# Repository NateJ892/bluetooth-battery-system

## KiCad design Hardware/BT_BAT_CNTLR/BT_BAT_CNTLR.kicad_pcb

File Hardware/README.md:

Bluetooth Battey Bank Project

TODO:
- Upsize regulator
- Add USB protection IC
- Increase Connector Current to 1.5A each for "Fast Charging"

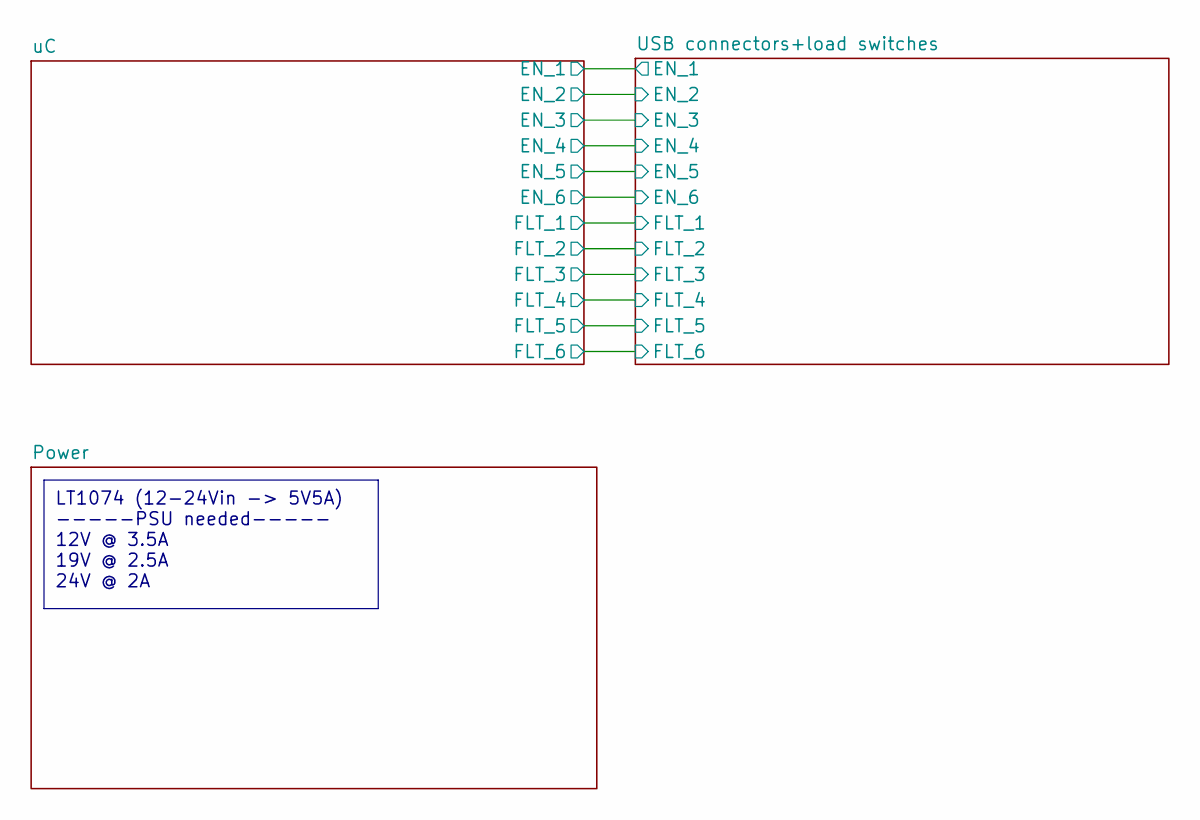
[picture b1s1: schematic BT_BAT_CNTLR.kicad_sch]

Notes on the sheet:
LT1074 (12-24Vin -> 5V5A) -----PSU needed----- 12V @ 3.5A 19V @ 2.5A 24V @ 2A

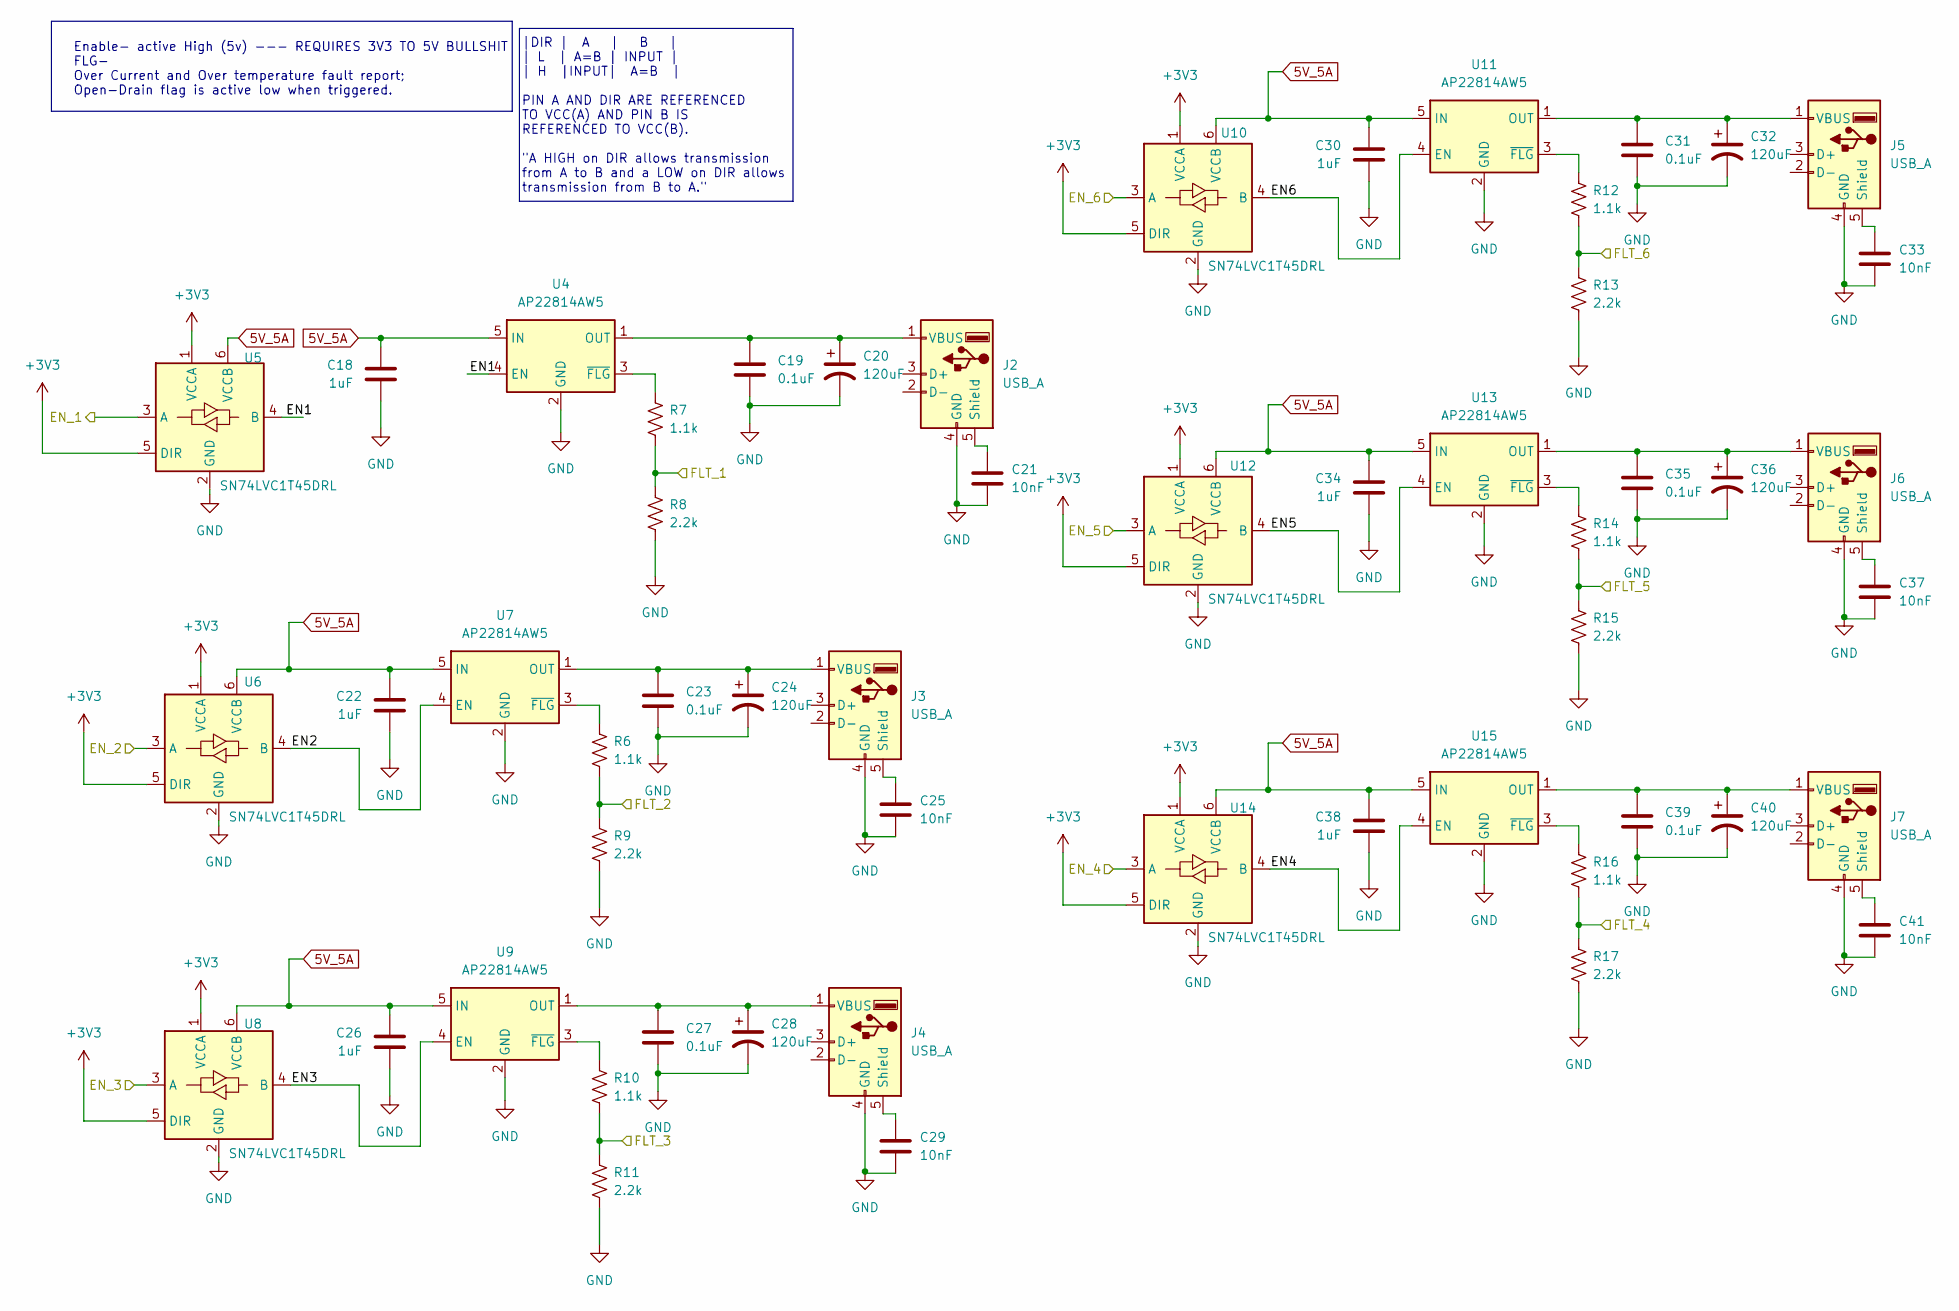
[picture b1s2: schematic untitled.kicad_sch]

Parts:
C18, C22, C26, C30, C34, C38: 1uF; C_0603_1608Metric
C19, C23, C27, C31, C35, C39: 0.1uF; C_0603_1608Metric
C20, C24, C28, C32, C36, C40: 120uF; CP_Elec_5x5.9
C21, C25, C29, C33, C37, C41: 10nF; C_0603_1608Metric
J2, J3, J4, J5, J6, J7: USB_A; USB_A_Molex_67643_Horizontal
R6, R7, R10, R12, R14, R16: 1.1k; R_0603_1608Metric
R8, R9, R11, R13, R15, R17: 2.2k; R_0603_1608Metric
U4, U7, U9, U11, U13, U15: AP22814AW5; SOT-23-5
U5, U6, U8, U10, U12, U14: SN74LVC1T45DRL; SOT-563

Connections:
5V_5A: C18.1, C22.1, C26.1, C30.1, C34.1, C38.1, U4.5 (IN), U5.6 (VCCB), U6.6 (VCCB), U7.5 (IN), U8.6 (VCCB), U9.5 (IN), U10.6 (VCCB), U11.5 (IN), U12.6 (VCCB), U13.5 (IN), U14.6 (VCCB), U15.5 (IN); also elsewhere on the board
+3V3: U5.1 (VCCA), U5.5 (DIR), U6.1 (VCCA), U6.5 (DIR), U8.1 (VCCA), U8.5 (DIR), U10.1 (VCCA), U10.5 (DIR), U12.1 (VCCA), U12.5 (DIR), U14.1 (VCCA), U14.5 (DIR); also elsewhere on the board
/USB connectors+load switches/EN1: U4.4 (EN), U5.4 (B)
/USB connectors+load switches/EN2: U6.4 (B), U7.4 (EN)
/USB connectors+load switches/EN3: U8.4 (B), U9.4 (EN)
/USB connectors+load switches/EN4: U14.4 (B), U15.4 (EN)
/USB connectors+load switches/EN5: U12.4 (B), U13.4 (EN)
/USB connectors+load switches/EN6: U10.4 (B), U11.4 (EN)
/USB connectors+load switches/EN_1: U5.3 (A); also elsewhere on the board
/USB connectors+load switches/EN_2: U6.3 (A); also elsewhere on the board
/USB connectors+load switches/EN_3: U8.3 (A); also elsewhere on the board
/USB connectors+load switches/EN_4: U14.3 (A); also elsewhere on the board
/USB connectors+load switches/EN_5: U12.3 (A); also elsewhere on the board
/USB connectors+load switches/EN_6: U10.3 (A); also elsewhere on the board
/USB connectors+load switches/FLT_1: R7.2, R8.1; also elsewhere on the board
/USB connectors+load switches/FLT_2: R6.2, R9.1; also elsewhere on the board
/USB connectors+load switches/FLT_3: R10.2, R11.1; also elsewhere on the board
/USB connectors+load switches/FLT_4: R16.2, R17.1; also elsewhere on the board
/USB connectors+load switches/FLT_5: R14.2, R15.1; also elsewhere on the board
/USB connectors+load switches/FLT_6: R12.2, R13.1; also elsewhere on the board
GND: C18.2, C19.2, C20.2, C21.2, C22.2, C23.2, C24.2, C25.2, C26.2, C27.2, C28.2, C29.2, C30.2, C31.2, C32.2, C33.2, C34.2, C35.2, C36.2, C37.2, C38.2, C39.2, C40.2, C41.2, J2.4 (GND), J3.4 (GND), J4.4 (GND), J5.4 (GND), J6.4 (GND), J7.4 (GND), R8.2, R9.2, R11.2, R13.2, R15.2, R17.2, U4.2 (GND), U5.2 (GND), U6.2 (GND), U7.2 (GND), U8.2 (GND), U9.2 (GND), U10.2 (GND), U11.2 (GND), U12.2 (GND), U13.2 (GND), U14.2 (GND), U15.2 (GND); also elsewhere on the board
unnamed: C21.1, J2.5 (Shield)
unnamed: C19.1, C20.1, J2.1 (VBUS), U4.1 (OUT)
unnamed: C25.1, J3.5 (Shield)
unnamed: C23.1, C24.1, J3.1 (VBUS), U7.1 (OUT)
unnamed: C29.1, J4.5 (Shield)
unnamed: C27.1, C28.1, J4.1 (VBUS), U9.1 (OUT)
unnamed: C33.1, J5.5 (Shield)
unnamed: C31.1, C32.1, J5.1 (VBUS), U11.1 (OUT)
unnamed: C37.1, J6.5 (Shield)
unnamed: C35.1, C36.1, J6.1 (VBUS), U13.1 (OUT)
unnamed: C41.1, J7.5 (Shield)
unnamed: C39.1, C40.1, J7.1 (VBUS), U15.1 (OUT)
unnamed: R7.1, U4.3 (~FLG)
unnamed: R6.1, U7.3 (~FLG)
unnamed: R10.1, U9.3 (~FLG)
unnamed: R12.1, U11.3 (~FLG)
unnamed: R14.1, U13.3 (~FLG)
unnamed: R16.1, U15.3 (~FLG)

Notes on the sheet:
|DIR | A | B | | L | A=B | INPUT | | H |INPUT| A=B | PIN A AND DIR ARE REFERENCED TO VCC(A) AND PIN B IS REFERENCED TO VCC(B). "A HIGH on DIR allows transmission from A to B and a LOW on DIR allows transmission from B to A."
Enable- active High (5v) --- REQUIRES 3V3 TO 5V BULLSHIT FLG- Over Current and Over temperature fault report; Open-Drain flag is active low when triggered.

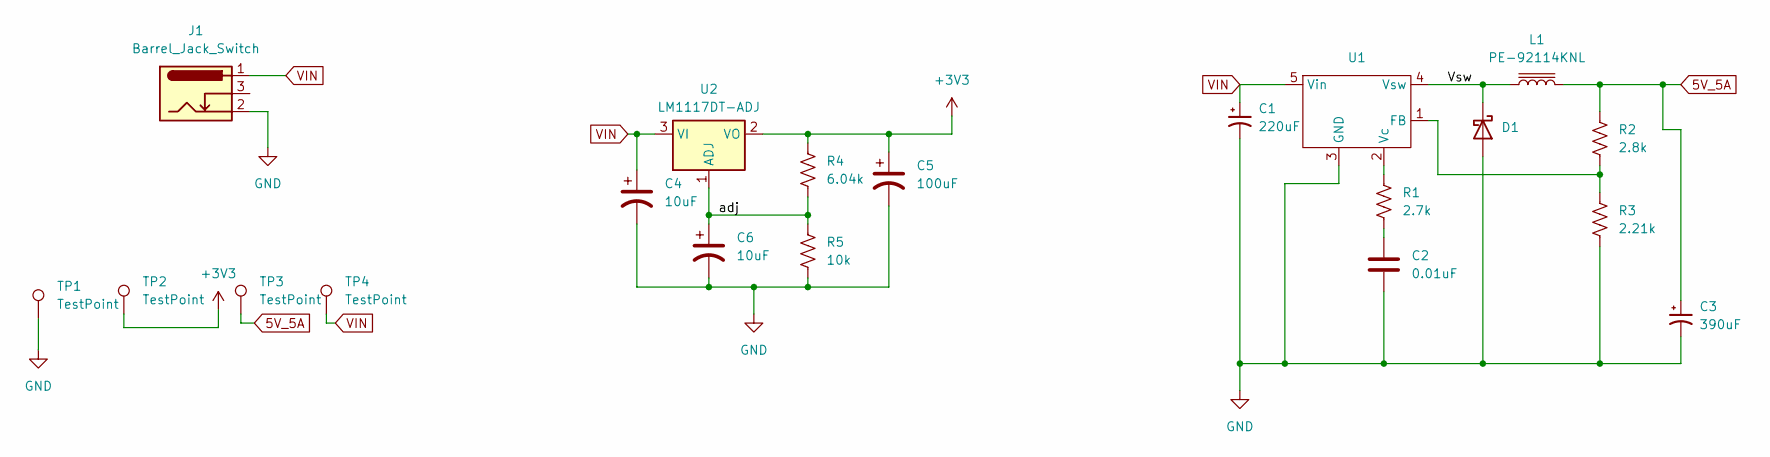
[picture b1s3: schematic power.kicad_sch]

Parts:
C1: 220uF; CP_Elec_10x10.5
C2: 0.01uF; C_0603_1608Metric
C3: 390uF; CP_Elec_10x10.5
C4, C6: 10uF; CP_Elec_4x4.5
C5: 100uF; CP_Elec_6.3x5.2
D1: D_Schottky; SK34BQ-L
J1: Barrel_Jack_Switch; BarrelJack_Wuerth_6941xx301002
L1: PE-92114KNL; PE-92114
R1: 2.7k; R_0603_1608Metric
R2: 2.8k; R_0603_1608Metric
R3: 2.21k; R_0603_1608Metric
R4: 6.04k; R_0603_1608Metric
R5: 10k; R_0603_1608Metric
TP1, TP2, TP3, TP4: TestPoint; TestPoint_Pad_D1.0mm
U1: TO-220-5_P3.4x3.8mm_StaggerOdd_Lead7.13mm_TabDown
U2: LM1117DT-ADJ; TO-252-3_TabPin2

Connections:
5V_5A: C3.1, L1.2, R2.1, TP3.1; also elsewhere on the board
+3V3: C5.1, R4.1, TP2.1, U2.2 (VO); also elsewhere on the board
/Power/Vsw: D1.1 (K), L1.1, U1.4 (Vsw)
/Power/adj: C6.1, R4.2, R5.1, U2.1 (ADJ)
GND: C1.2, C2.2, C3.2, C4.2, C5.2, C6.2, D1.2 (A), J1.2, R3.2, R5.2, TP1.1, U1.3 (GND); also elsewhere on the board
unnamed: C2.1, R1.2
unnamed: R2.2, R3.1, U1.1 (FB)
unnamed: R1.1, U1.2 (Vc)
VIN: C1.1, C4.1, J1.1, TP4.1, U1.5 (Vin), U2.3 (VI)

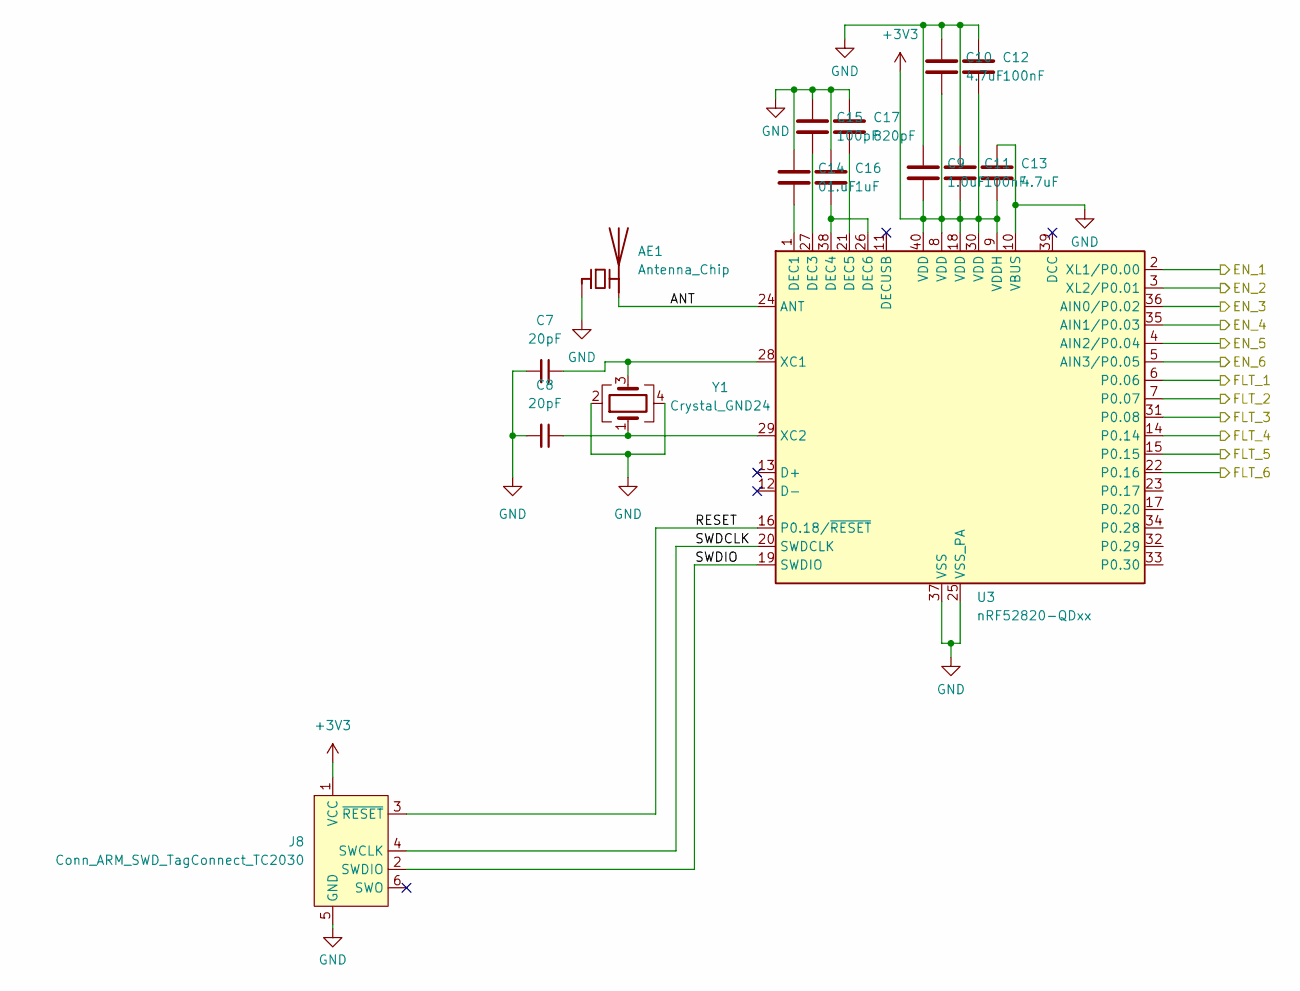
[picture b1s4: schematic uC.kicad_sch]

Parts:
AE1: Antenna_Chip; Texas_SWRA117D_2.4GHz_Right
C7, C8: 20pF; C_0402_1005Metric
C9: 1.0uF; C_0603_1608Metric
C10, C13: 4.7uF; C_0603_1608Metric
C11, C12: 100nF; C_0603_1608Metric
C14: 01.uF; C_0603_1608Metric
C15: 100pF; C_0603_1608Metric
C16: 1uF; C_0603_1608Metric
C17: 820pF; C_0603_1608Metric
J8: Conn_ARM_SWD_TagConnect_TC2030; Tag-Connect_TC2030-IDC-FP_2x03_P1.27mm_Vertical
U3: nRF52820-QDxx; QFN-40-1EP_5x5mm_P0.4mm_EP3.6x3.6mm
Y1: Crystal_GND24; Oscillator_SMD_Kyocera_KC2520Z-4Pin_2.5x2.0mm

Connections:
+3V3: C9.2, C10.2, C11.2, C12.2, C13.2, J8.1 (VCC), U3.8 (VDD), U3.9 (VDDH), U3.18 (VDD), U3.30 (VDD), U3.40 (VDD); also elsewhere on the board
/USB connectors+load switches/EN_1: U3.2 (XL1/P0.00); also elsewhere on the board
/USB connectors+load switches/EN_2: U3.3 (XL2/P0.01); also elsewhere on the board
/USB connectors+load switches/EN_3: U3.36 (AIN0/P0.02); also elsewhere on the board
/USB connectors+load switches/EN_4: U3.35 (AIN1/P0.03); also elsewhere on the board
/USB connectors+load switches/EN_5: U3.4 (AIN2/P0.04); also elsewhere on the board
/USB connectors+load switches/EN_6: U3.5 (AIN3/P0.05); also elsewhere on the board
/USB connectors+load switches/FLT_1: U3.6 (P0.06); also elsewhere on the board
/USB connectors+load switches/FLT_2: U3.7 (P0.07); also elsewhere on the board
/USB connectors+load switches/FLT_3: U3.31 (P0.08); also elsewhere on the board
/USB connectors+load switches/FLT_4: U3.14 (P0.14); also elsewhere on the board
/USB connectors+load switches/FLT_5: U3.15 (P0.15); also elsewhere on the board
/USB connectors+load switches/FLT_6: U3.22 (P0.16); also elsewhere on the board
/uC/ANT: AE1.2 (PCB_Trace), U3.24 (ANT)
/uC/RESET: J8.3 (~RESET), U3.16 (P0.18/~RESET)
/uC/SWDCLK: J8.4 (SWCLK), U3.20 (SWDCLK)
/uC/SWDIO: J8.2 (SWDIO), U3.19 (SWDIO)
GND: AE1.1 (FEED), C7.2, C8.2, C9.1, C10.1, C11.1, C12.1, C13.1, C14.1, C15.1, C16.1, C17.1, J8.5 (GND), U3.10 (VBUS), U3.25 (VSS_PA), U3.37 (VSS), U3.41 (VSS), Y1.2, Y1.4; also elsewhere on the board
unnamed: C14.2, U3.1 (DEC1)
unnamed: C15.2, U3.27 (DEC3)
unnamed: C16.2, U3.26 (DEC6), U3.38 (DEC4)
unnamed: C17.2, U3.21 (DEC5)
unnamed: C7.1, U3.28 (XC1), Y1.3
unnamed: C8.1, U3.29 (XC2), Y1.1

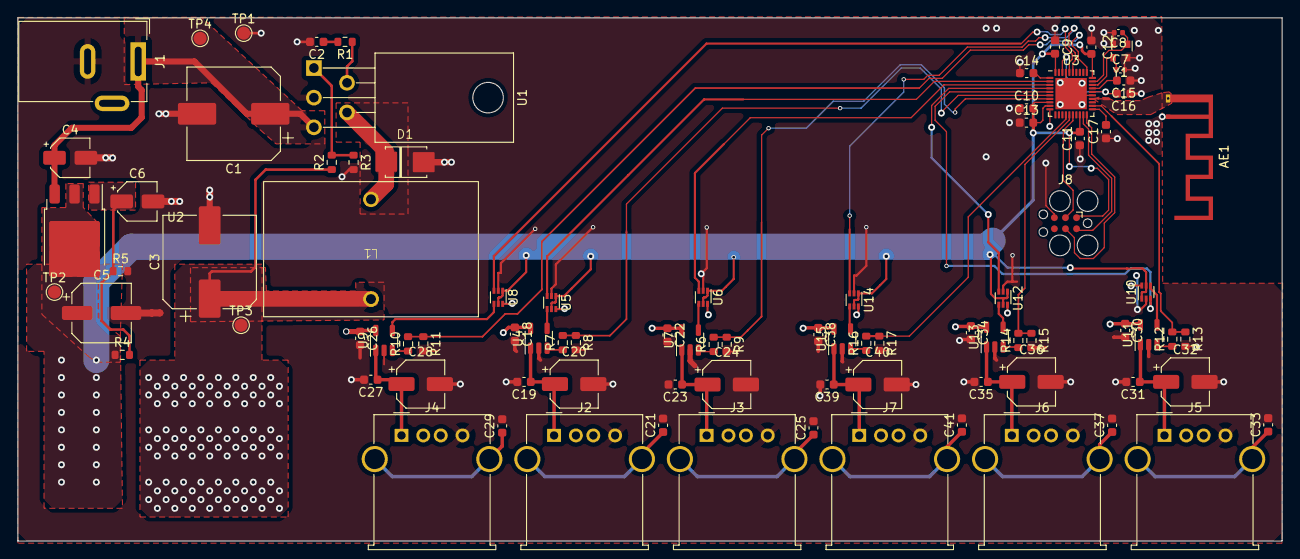
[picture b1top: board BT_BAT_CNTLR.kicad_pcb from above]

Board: 2 copper layers, 145.0 x 60.0 mm, 89 parts (0 on the bottom side), 55 nets.

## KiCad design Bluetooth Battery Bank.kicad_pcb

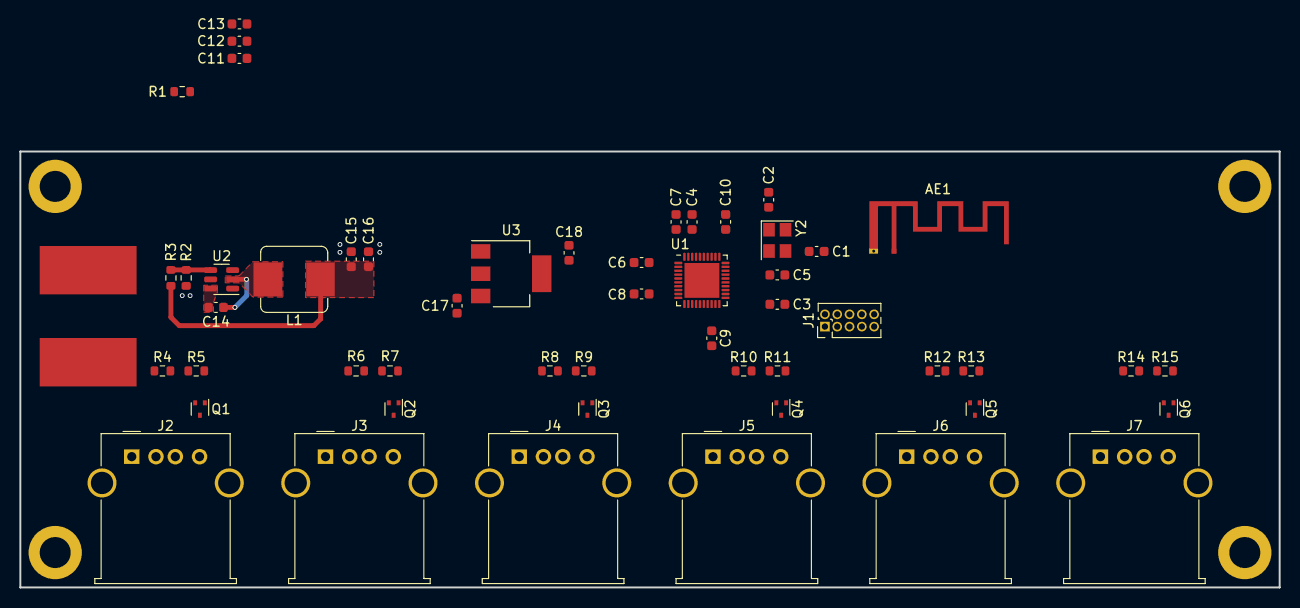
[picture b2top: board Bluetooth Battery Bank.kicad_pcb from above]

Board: 2 copper layers, 130.0 x 45.0 mm, 58 parts (0 on the bottom side), 36 nets.

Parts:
AE1: Antenna; Texas_SWRA117D_2.4GHz_Right
C1, C2: 20pF; C_0603_1608Metric
C3: 820pF; C_0603_1608Metric
C4, C7, C17, C18: 1uF; C_0603_1608Metric
C5: 100pF; C_0603_1608Metric
C6, C9, C10, C13, C14: 0.1uF; C_0603_1608Metric
C8: 4.7uF; C_0603_1608Metric
C11, C12: 10uF; C_0603_1608Metric
C15, C16: 22uF; C_0603_1608Metric
H1, H2, H3, H4: MountingHole_Pad; MountingHole_3.2mm_M3_ISO14580_Pad
J1: Conn_02x05_Odd_Even; PinHeader_2x05_P1.27mm_Vertical
J2, J3, J4, J5, J6, J7: USB_A; USB_A_Molex_67643_Horizontal
J8, J9: Conn_01x01_Pin; SolderWirePad_1x01_SMD_5x10mm
L1: 3.3uH; L_Bourns_SRP7028A_7.3x6.6mm
Q1, Q2, Q3, Q4, Q5, Q6: DMG1012T; SOT-523
R1, R2, R4, R6, R8, R10, R12, R14: 10K; R_0603_1608Metric
R3: 54.9K; R_0603_1608Metric
R5, R7, R9, R11, R13, R15: 165; R_0603_1608Metric
U1: nRF52820-QDxx; QFN-40-1EP_5x5mm_P0.4mm_EP3.6x3.6mm
U2: TPS565208; SOT-23-6
U3: TLV1117LV33DCYR; SOT-223-3_TabPin2
Y2: Crystal_GND24; Crystal_SMD_3225-4Pin_3.2x2.5mm

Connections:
+3V3: C7.1, C8.1, C9.1, C10.1, C18.1, J1.1, U1.8 (VDD), U1.9 (VDDH), U1.18 (VDD), U1.30 (VDD), U1.40 (VDD), U3.2 (VO)
+5V: C15.2, C16.2, C17.1, J2.1 (VBUS), J3.1 (VBUS), J4.1 (VBUS), J5.1 (VBUS), J6.1 (VBUS), J7.1 (VBUS), L1.1, R3.2, U3.3 (VI)
/SWDCLK: J1.4, U1.20 (SWDCLK)
/SWDIO: J1.2, U1.19 (SWDIO)
/USB Connectors/EN_1: R4.2, R5.1, U1.2 (XL1/P0.00)
/USB Connectors/EN_2: R6.2, R7.1, U1.3 (XL2/P0.01)
/USB Connectors/EN_3: R8.2, R9.1, U1.36 (AIN0/P0.02)
/USB Connectors/EN_4: R10.2, R11.1, U1.35 (AIN1/P0.03)
/USB Connectors/EN_5: R12.2, R13.1, U1.4 (AIN2/P0.04)
/USB Connectors/EN_6: R14.2, R15.1, U1.5 (AIN3/P0.05)
/~RESET: J1.10, U1.16 (P0.18/~RESET)
GND: AE1.2 (PCB_Trace), C1.1, C2.1, C3.1, C4.1, C5.1, C6.1, C7.2, C8.2, C9.2, C10.2, C11.2, C12.2, C13.2, C15.1, C16.1, C17.2, C18.2, H1.1, H2.1, H3.1, H4.1, J1.3, J1.5, J1.9, J9.1, Q1.2 (S), Q2.2 (S), Q3.2 (S), Q4.2 (S), Q5.2 (S), Q6.2 (S), R2.1, R4.1, R6.1, R8.1, R10.1, R12.1, R14.1, U1.10 (VBUS), U1.25 (VSS_PA), U1.37 (VSS), U1.41 (VSS), U2.1 (GND), U3.1 (GND), Y2.2, Y2.4
unnamed: AE1.1 (FEED), U1.24 (ANT)
unnamed: J2.4 (GND), Q1.3 (D)
unnamed: J3.4 (GND), Q2.3 (D)
unnamed: J4.4 (GND), Q3.3 (D)
unnamed: J5.4 (GND), Q4.3 (D)
unnamed: J6.4 (GND), Q5.3 (D)
unnamed: J7.4 (GND), Q6.3 (D)
unnamed: Q1.1 (G), R5.2
unnamed: Q2.1 (G), R7.2
unnamed: Q3.1 (G), R9.2
unnamed: Q4.1 (G), R11.2
unnamed: Q5.1 (G), R13.2
unnamed: Q6.1 (G), R15.2
unnamed: C6.2, U1.1 (DEC1)
unnamed: C5.2, U1.27 (DEC3)
unnamed: C4.2, U1.26 (DEC6), U1.38 (DEC4)
unnamed: C3.2, U1.21 (DEC5)
unnamed: C1.2, U1.28 (XC1), Y2.3
unnamed: C2.2, U1.29 (XC2), Y2.1
unnamed: R1.2, U2.5 (EN)
unnamed: C14.2, L1.2, U2.2 (SW)
unnamed: C14.1, U2.6 (VBST)
unnamed: R2.2, R3.1, U2.4 (VFB)
VCC: C11.1, C12.1, C13.1, J8.1, R1.1, U2.3 (VIN)

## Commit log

2023-12-31 Inital Push to Github
2023-12-31 Squashed commit of the following:
    commit 1240e276bba30743f625476e3868482a3f1d4b58
    Author: NateJ892 <42608819+NateJ892@users.noreply.github.com>
    Date: Sun Dec 31 11:42:26 2023 -0500
    Create README.md
2023-12-31 Move Kicad Project to seperate folder
2024-01-03 initial commit
    12VIN>5V5A parts selected and placed. Polygons need to be cleaned.
2024-01-03 added LM1117 Calculations
2024-01-04 dead ass think I just added a second copy..
    aight. routed caps and antenna for nRF.
    need to route power and find a new IC for USB ports.
2024-01-04 Added 1 USB circuit
    will wait for approval/ review before continuing
2024-01-04 Added 5x more USB things
    also fanned out the nRF
2024-01-05 Add gitignore for "backups"
2024-01-05 Add gitignore for "backups" & KiCAD lock (.lck) files" Untrack all backup files
2024-01-05 did a bit of things
    added the forgotten programmer header
    did some routing and then got lazy with it (a lot can be cleaned up)
    need to change the 12v>5v reg still
    need to change the 12vin connector
2024-01-05 did a bit of stuff
    same stuff I added in master-
    lazy routing- added programming connector.
    thats about it
2024-01-24 - Github Tree Cleanup - Power Routing
2024-02-21 Need Help
2024-02-21 routed
    reorganized some components. traces and vias need to be conforming. Silk needs to be reorganized.
